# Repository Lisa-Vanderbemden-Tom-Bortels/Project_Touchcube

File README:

Hier zijn alle bestanden terug te vinden van het project: Project Touchcube van Tom Bortels en Lisa Vanderbemden,
studenten Electronica - ICT op PXL Tech in Diepenbeek

Om het programma met de sensor te kunnen gebruiken zijn er eerst een aantal kleine aanpassingen nodig.

Eerst moet er een database worden aangemaakt, dit kan lokaal of op een online server.
Het is aan te raden een MySQL database te gebruiken. Het is in principe ook mogelijk een andere database te gebruiken, maar dan moeten de References in het C# programma aangepast worden naar de juiste soort database.

De naam van de database hoor a2100359_project te zijn. Het kan ook een andere naam krijgen, mits deze naam ook aangepast wordt in Connection.cs van het C# programma
Vervolgens kan het script a2100359_project(2).sql gebruikt worden om alle tabellen aan te maken en deze te vullen met benodigde waarde.

Voor het programma gestart kan worden moet in het bestand connection.cs eerst nog de gebruikersnaam en wachtwoord van de Mysqldatabase worden ingevuld. Voor beveiligingsredenen zijn deze verwijderd uit dit bestand.
Hierna kan het C# programma gestart word. Er wordt een login gevraagd. Er is een test user met administratorrechten :
 gebruikersnaam: 10    wachtwoord: pxltech

Hierna kan het programma werken zoals voorzien.

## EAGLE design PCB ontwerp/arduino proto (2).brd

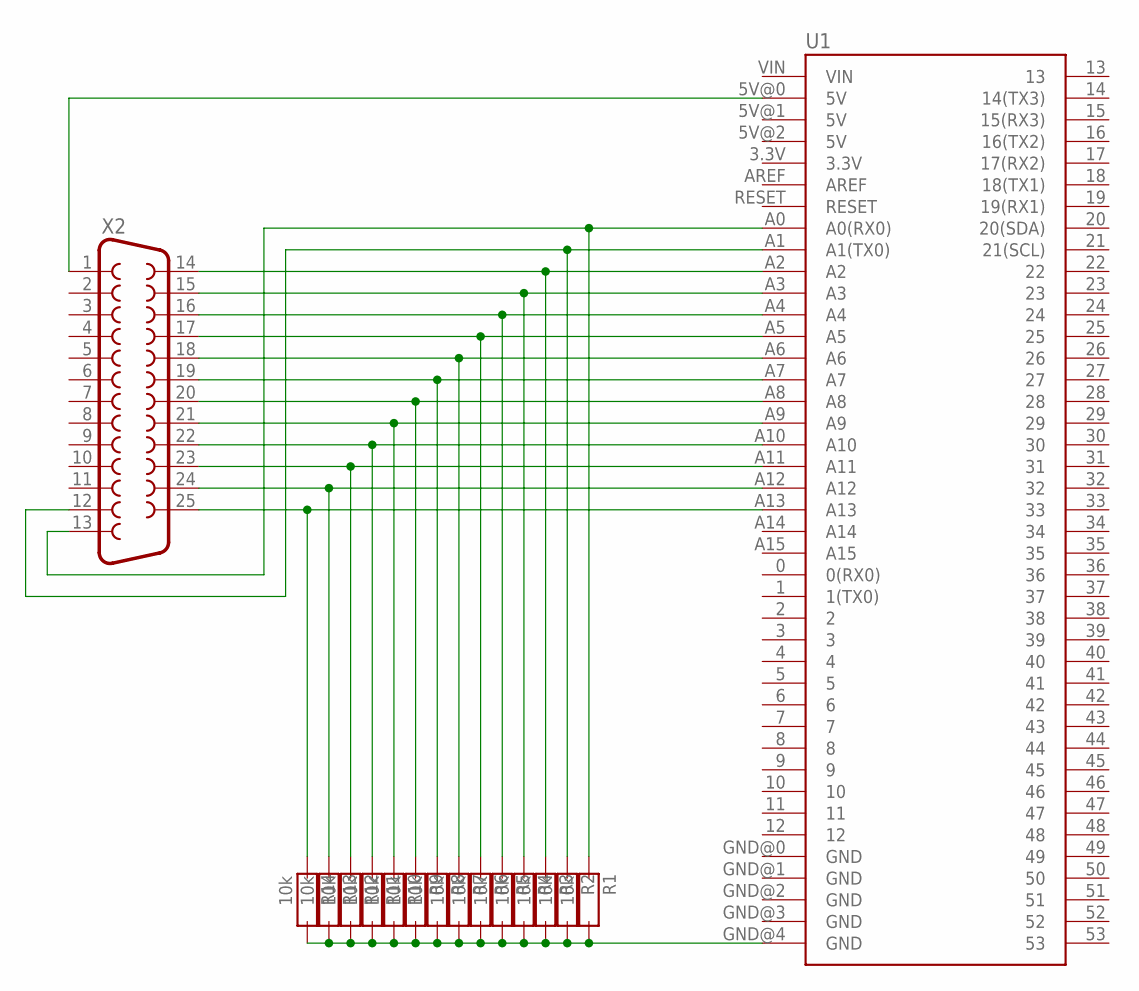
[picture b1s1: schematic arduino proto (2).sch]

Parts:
R1, R2, R3, R4, R5, R6, R7, R8, R9, R10, R11, R12, R13, R14: 10k; AX3
U1: ARDUINO-MEGAFULL; ARDUINO_MEGA
X2: F25HP

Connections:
unnamed: R14.1, U1.A13, X2.25
unnamed: R13.1, U1.A12, X2.24
unnamed: R12.1, U1.A11, X2.23
unnamed: R11.1, U1.A10, X2.22
unnamed: R10.1, U1.A9, X2.21
unnamed: R9.1, U1.A8, X2.20
unnamed: R8.1, U1.A7, X2.19
unnamed: R7.1, U1.A6, X2.18
unnamed: R6.1, U1.A5, X2.17
unnamed: R5.1, U1.A4, X2.16
unnamed: R4.1, U1.A3, X2.15
unnamed: R3.1, U1.A2, X2.14
unnamed: R2.1, U1.A1 (A1(TX0)), X2.12
unnamed: R1.1, U1.A0 (A0(RX0)), X2.13
unnamed: U1.5V@0 (5V), X2.1
unnamed: R1.2, R2.2, R3.2, R4.2, R5.2, R6.2, R7.2, R8.2, R9.2, R10.2, R11.2, R12.2, R13.2, R14.2, U1.GND@4 (GND)

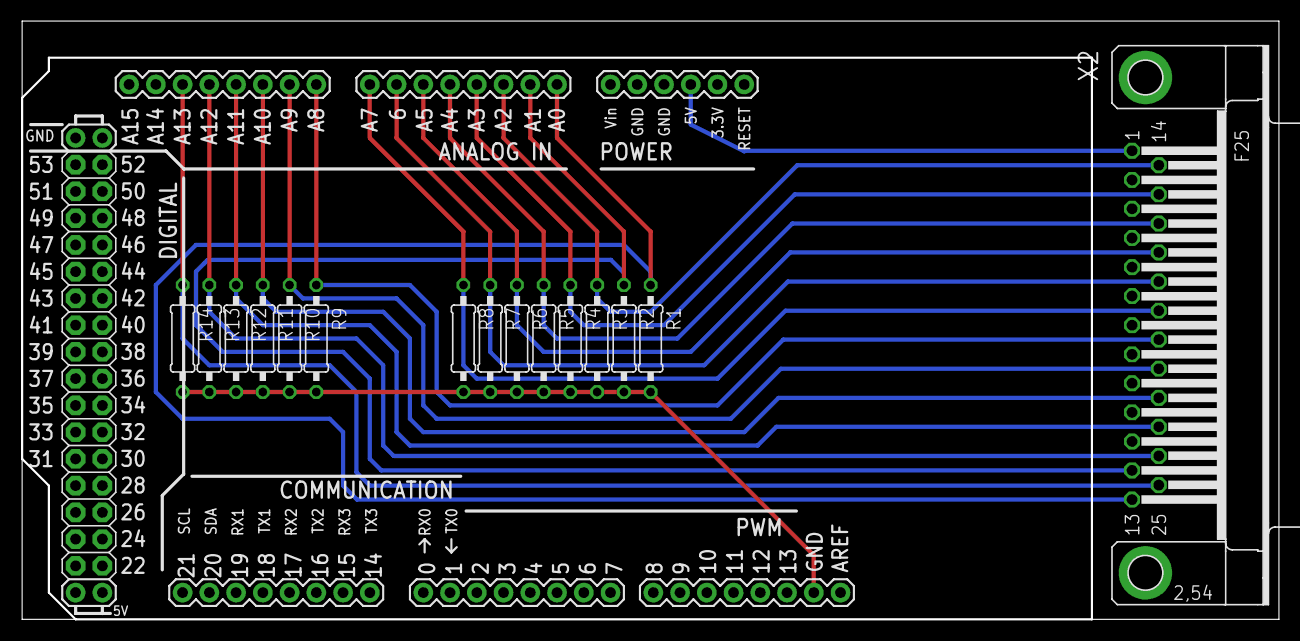
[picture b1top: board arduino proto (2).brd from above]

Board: 2 copper layers, 119.3 x 56.7 mm, 16 parts (0 on the bottom side), 16 nets.

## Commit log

2014-06-04 Versie project
    Dit is zeer waarschijnlijk de finale versie van dit project.

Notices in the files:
parts and their libraries:
SparkFun-Connectors: Licensing: CC v3.0 Share-Alike You are welcome to use this library for commercial purposes.
